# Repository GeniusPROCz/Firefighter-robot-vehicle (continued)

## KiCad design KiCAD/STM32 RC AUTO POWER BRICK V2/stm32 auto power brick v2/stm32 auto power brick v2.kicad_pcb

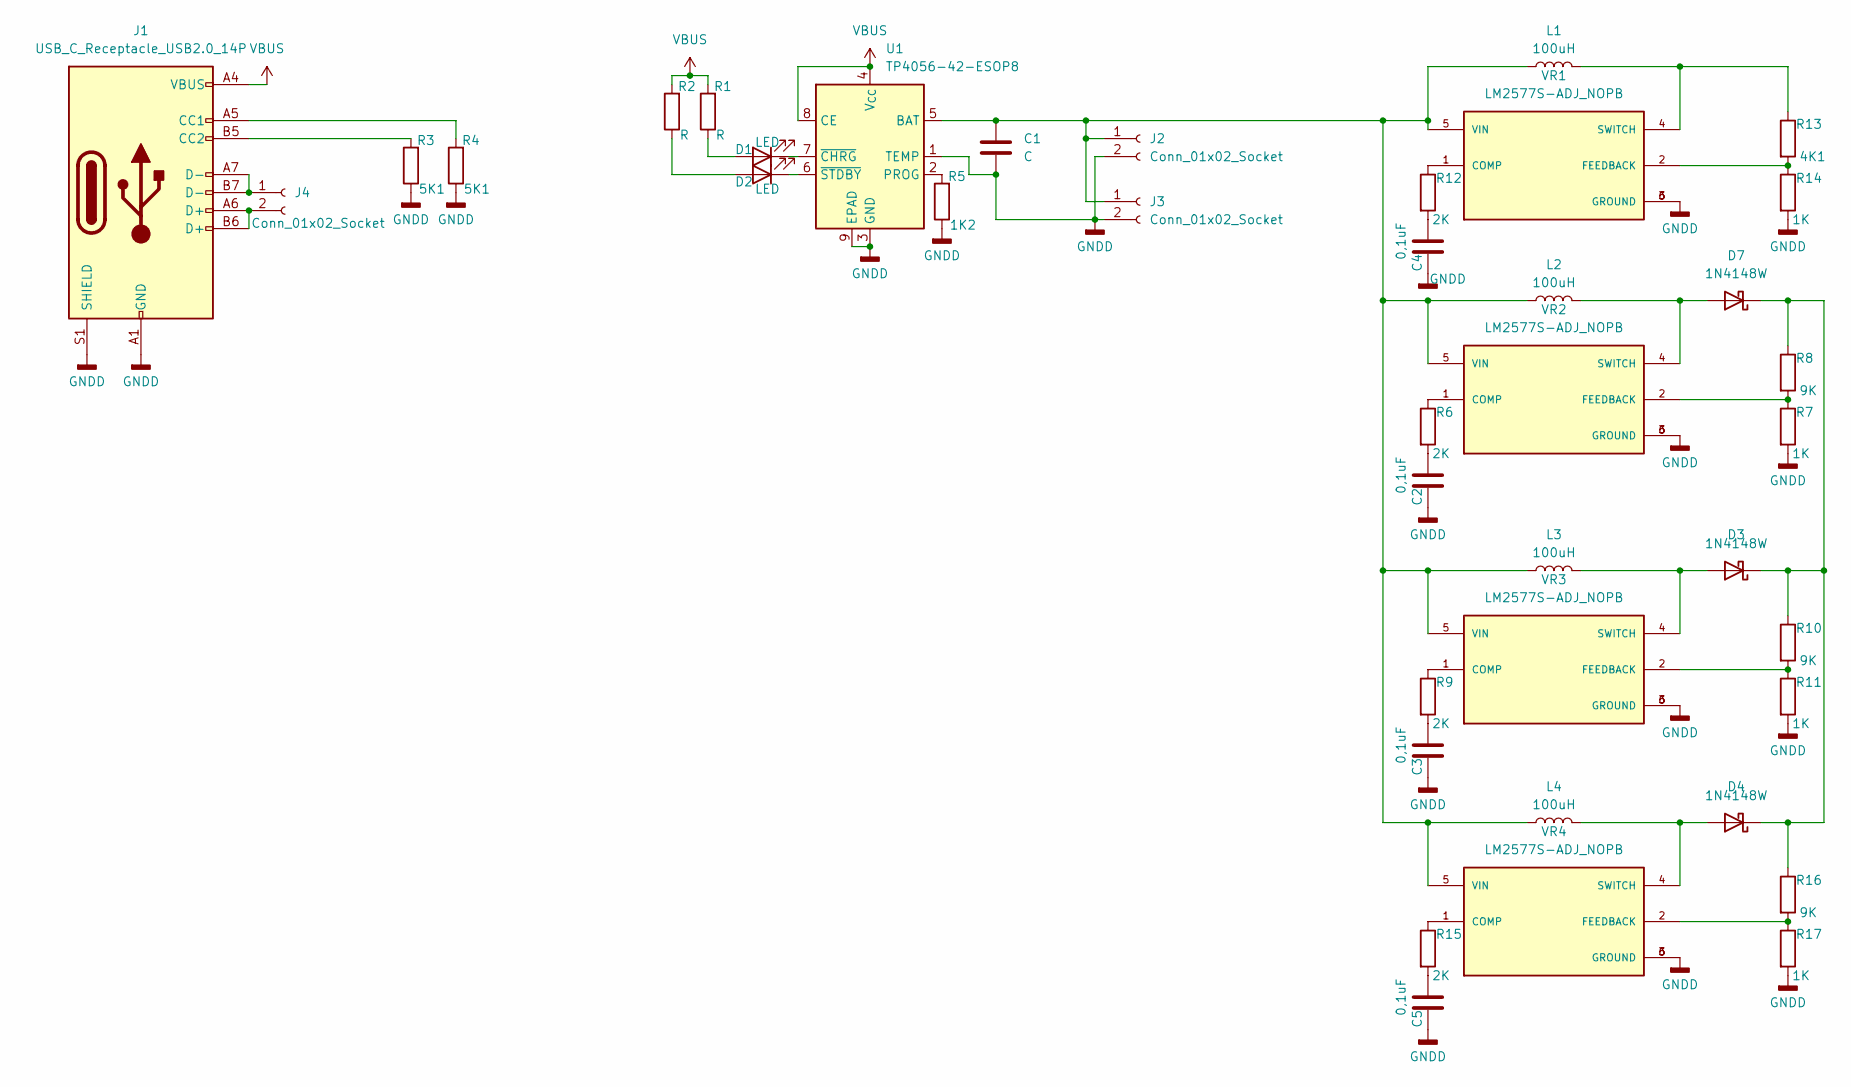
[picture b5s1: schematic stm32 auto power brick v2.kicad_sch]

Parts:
C1: C; C_0805_2012Metric_Pad1.18x1.45mm_HandSolder
C2, C3, C4, C5: 0,1uF; C_0805_2012Metric_Pad1.18x1.45mm_HandSolder
D1, D2: LED; LED_0805_2012Metric_Pad1.15x1.40mm_HandSolder
D3, D4, D7: 1N4148W; D_SOD-123F
J1: USB_C_Receptacle_USB2.0_14P; USB_C_Receptacle_G-Switch_GT-USB-7010ASV_model
J2, J3: Conn_01x02_Socket
J4: Conn_01x02_Socket; JST_XH_B2B-XH-A_1x02_P2.50mm_Vertical
L1, L2, L3, L4: 100uH; L_12x12mm_H4.5mm_model
R1, R2: R; R_0805_2012Metric_Pad1.20x1.40mm_HandSolder
R3, R4: 5K1; R_0805_2012Metric_Pad1.20x1.40mm_HandSolder
R5: 1K2; R_0805_2012Metric_Pad1.20x1.40mm_HandSolder
R6, R9, R12, R15: 2K; R_0805_2012Metric_Pad1.20x1.40mm_HandSolder
R7, R11, R14, R17: 1K; R_0805_2012Metric_Pad1.20x1.40mm_HandSolder
R8, R10, R16: 9K; R_0805_2012Metric_Pad1.20x1.40mm_HandSolder
R13: 4K1; R_0805_2012Metric_Pad1.20x1.40mm_HandSolder
U1: TP4056-42-ESOP8; SOIC-8-1EP_3.9x4.9mm_P1.27mm_EP2.41x3.3mm_ThermalVias_model
VR1, VR2, VR3, VR4: LM2577S-ADJ_NOPB; VREG_LM2577S-ADJ_NOPB_model; PARTREV D

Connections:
GNDD: C1.2, C2.1, C3.1, C4.1, C5.1, J1.A1 (GND), J1.A12 (GND), J1.B1 (GND), J1.B12 (GND), J1.S1 (SHIELD), J2.2, J3.2, R3.1, R4.1, R5.1, R7.2, R11.2, R14.2, R17.2, U1.1 (TEMP), U1.3 (GND), U1.9 (EPAD), VR1.3 (GROUND), VR1.6 (GROUND), VR2.3 (GROUND), VR2.6 (GROUND), VR3.3 (GROUND), VR3.6 (GROUND), VR4.3 (GROUND), VR4.6 (GROUND)
unnamed: C2.2, R6.2
unnamed: C3.2, R9.2
unnamed: C4.2, R12.2
unnamed: C5.2, R15.2
unnamed: D1.2 (A), R1.1
unnamed: D1.1 (K), U1.7 (~CHRG)
unnamed: D2.2 (A), R2.1
unnamed: D2.1 (K), U1.6 (~STDBY)
unnamed: D3.2 (A), L3.2, VR3.4 (SWITCH)
unnamed: D3.1 (K), D4.1 (K), D7.1 (K), R8.1, R10.1, R16.1
unnamed: D4.2 (A), L4.2, VR4.4 (SWITCH)
unnamed: D7.2 (A), L2.2, VR2.4 (SWITCH)
unnamed: J1.A5 (CC1), R4.2
unnamed: J1.B5 (CC2), R3.2
unnamed: C1.1, J2.1, J3.1, L1.1, L2.1, L3.1, L4.1, U1.5 (BAT), VR1.5 (VIN), VR2.5 (VIN), VR3.5 (VIN), VR4.5 (VIN)
unnamed: J1.A7 (D-), J1.B7 (D-), J4.1
unnamed: J1.A6 (D+), J1.B6 (D+), J4.2
unnamed: R5.2, U1.2 (PROG)
unnamed: R12.1, VR1.1 (COMP)
unnamed: R13.2, R14.1, VR1.2 (FEEDBACK)
unnamed: L1.2, R13.1, VR1.4 (SWITCH)
unnamed: R6.1, VR2.1 (COMP)
unnamed: R7.1, R8.2, VR2.2 (FEEDBACK)
unnamed: R9.1, VR3.1 (COMP)
unnamed: R10.2, R11.1, VR3.2 (FEEDBACK)
unnamed: R15.1, VR4.1 (COMP)
unnamed: R16.2, R17.1, VR4.2 (FEEDBACK)
VBUS: J1.A4 (VBUS), J1.A9 (VBUS), J1.B4 (VBUS), J1.B9 (VBUS), R1.2, R2.2, U1.4 (V_{CC}), U1.8 (CE)

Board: 8 copper layers, 38 parts (4 on the bottom side), 29 nets, no tracks yet.

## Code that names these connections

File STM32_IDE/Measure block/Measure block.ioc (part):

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Mcu.Name=STM32F030C8Tx
Mcu.Package=LQFP48
Mcu.UserName=STM32F030C8Tx
PA0.Mode=IN0
PA0.Signal=ADC_IN0
PA1.Mode=IN1
PA1.Signal=ADC_IN1
PA13.Mode=Serial_Wire
PA13.Signal=SYS_SWDIO
PA14.Mode=Serial_Wire
PA14.Signal=SYS_SWCLK
PA2.Mode=IN2
PA2.Signal=ADC_IN2
PA3.Mode=IN3
PA3.Signal=ADC_IN3
PA4.Mode=IN4
PA4.Signal=ADC_IN4
PA5.Mode=IN5
PA5.Signal=ADC_IN5
PB1.Signal=GPIO_Output
PB13.Mode=Full_Duplex_Master
PB13.Signal=SPI2_SCK
PB14.Mode=Full_Duplex_Master
PB14.Signal=SPI2_MISO
PB15.Mode=Full_Duplex_Master
PB15.Signal=SPI2_MOSI
PB2.Signal=GPIO_Output
PB3.Mode=Full_Duplex_Master
PB3.Signal=SPI1_SCK
PB4.Mode=Full_Duplex_Master
PB4.Signal=SPI1_MISO
PB5.Mode=Full_Duplex_Master
PB5.Signal=SPI1_MOSI
PB6.Mode=I2C
PB6.Signal=I2C1_SCL
PB7.Mode=I2C
PB7.Signal=I2C1_SDA
PC14-OSC32_IN.Mode=LSE-External-Oscillator
PC14-OSC32_IN.Signal=RCC_OSC32_IN
PC15-OSC32_OUT.Mode=LSE-External-Oscillator
PC15-OSC32_OUT.Signal=RCC_OSC32_OUT
PF0-OSC_IN.Mode=HSE-External-Oscillator
PF0-OSC_IN.Signal=RCC_OSC_IN
PF1-OSC_OUT.Mode=HSE-External-Oscillator
PF1-OSC_OUT.Signal=RCC_OSC_OUT
RCC.HSE_VALUE=25000000
RCC.SYSCLKFreq_VALUE=48000000
RCC.SYSCLKSource=RCC_SYSCLKSOURCE_PLLCLK
board=custom

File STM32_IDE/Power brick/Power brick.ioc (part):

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Mcu.Name=STM32F411R(C-E)Tx
Mcu.Package=LQFP64
Mcu.UserName=STM32F411RCTx
PA10.Signal=S_TIM1_CH3
PA11.Signal=S_TIM1_CH4
PA13.Mode=Serial_Wire
PA13.Signal=SYS_JTMS-SWDIO
PA14.Mode=Serial_Wire
PA14.Signal=SYS_JTCK-SWCLK
PA3.Signal=GPIO_Output
PA4.Signal=SPI1_NSS
PA5.Mode=Full_Duplex_Slave
PA5.Signal=SPI1_SCK
PA6.Mode=Full_Duplex_Slave
PA6.Signal=SPI1_MISO
PA7.Mode=Full_Duplex_Slave
PA7.Signal=SPI1_MOSI
PA8.Signal=S_TIM1_CH1
PA9.Signal=S_TIM1_CH2
PB0.Signal=GPIO_Output
PB1.Signal=GPIO_Output
PC10.Signal=GPIO_Output
PC11.Signal=GPIO_Output
PC4.Signal=GPIO_Output
PC5.Signal=GPIO_Output
PC6.Signal=S_TIM3_CH1
PC7.Signal=S_TIM3_CH2
PC8.Signal=S_TIM3_CH3
PC9.Signal=S_TIM3_CH4
PH0\ -\ OSC_IN.Mode=HSE-External-Oscillator
PH0\ -\ OSC_IN.Signal=RCC_OSC_IN
PH1\ -\ OSC_OUT.Mode=HSE-External-Oscillator
PH1\ -\ OSC_OUT.Signal=RCC_OSC_OUT
RCC.HSE_VALUE=25000000
RCC.SYSCLKFreq_VALUE=100000000
RCC.SYSCLKSource=RCC_SYSCLKSOURCE_PLLCLK
board=custom

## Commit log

2025-11-11 Adding half done projects
2025-11-11 i dont know
2025-11-12 save of shcematic
2025-11-12 Motor power brick implementation
2025-11-12 Multi ADD
    Completed work version of code and did more work on schematic
2025-11-19 adding completation on schematic, working on board
    need to add SWD Debug as input for programing
2025-12-04 .
    .
